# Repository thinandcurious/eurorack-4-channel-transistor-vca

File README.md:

# eurorack-4-channel-transistor-vca

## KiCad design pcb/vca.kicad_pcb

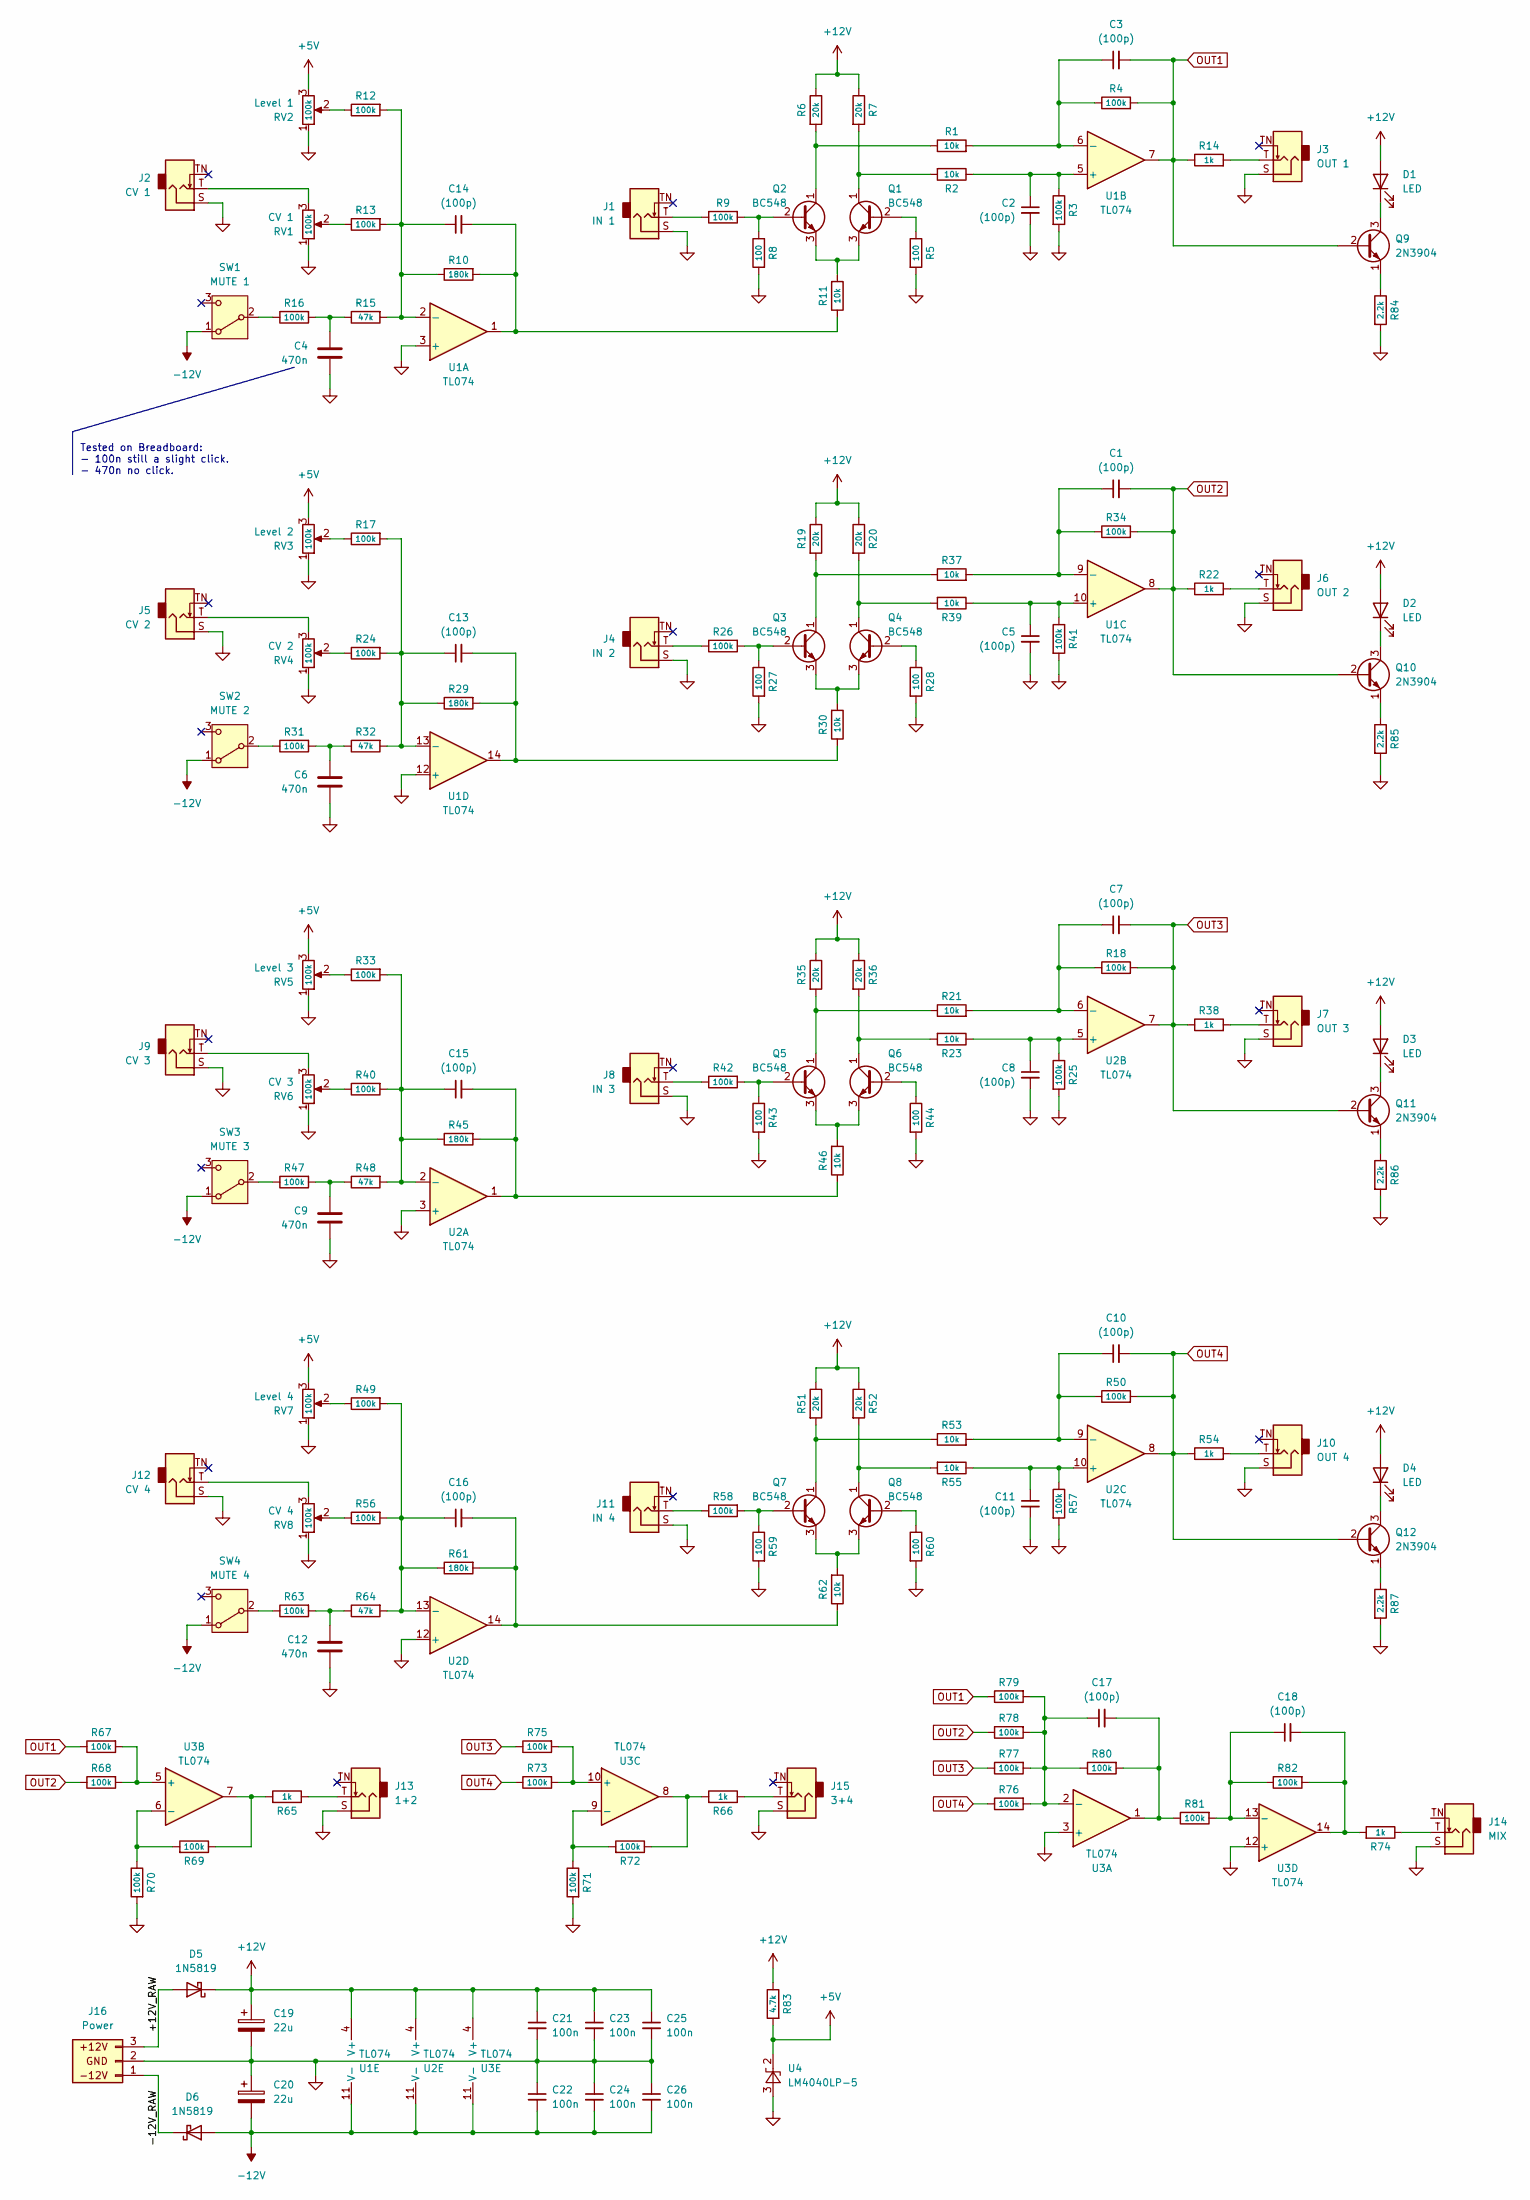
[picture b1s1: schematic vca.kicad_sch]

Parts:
C1, C2, C3, C5, C7, C8, C10, C11, C13, C14, C15, C16, C17, C18: (100p); C_0805_HandSolder
C4, C6, C9, C12: 470n; C_Rect_L7.2mm_W3.0mm_P5.00mm_FKS2_FKP2_MKS2_MKP2
C19, C20: 22u; CP_Radial_D6.3mm_P2.50mm
C21, C22, C23, C24, C25, C26: 100n; C_0805_HandSolder
D1, D2, D3, D4: LED; LED_D3.0mm_Centered
D5, D6: 1N5819; D_DO-41_SOD81_P7.62mm_Horizontal
J1: IN 1; Jack_3.5mm_PJ398SM_Vertical
J2: CV 1; Jack_3.5mm_PJ398SM_Vertical
J3: OUT 1; Jack_3.5mm_PJ398SM_Vertical
J4: IN 2; Jack_3.5mm_PJ398SM_Vertical
J5: CV 2; Jack_3.5mm_PJ398SM_Vertical
J6: OUT 2; Jack_3.5mm_PJ398SM_Vertical
J7: OUT 3; Jack_3.5mm_PJ398SM_Vertical
J8: IN 3; Jack_3.5mm_PJ398SM_Vertical
J9: CV 3; Jack_3.5mm_PJ398SM_Vertical
J10: OUT 4; Jack_3.5mm_PJ398SM_Vertical
J11: IN 4; Jack_3.5mm_PJ398SM_Vertical
J12: CV 4; Jack_3.5mm_PJ398SM_Vertical
J13: 1+2; Jack_3.5mm_PJ398SM_Vertical
J14: MIX; Jack_3.5mm_PJ398SM_Vertical
J15: 3+4; Jack_3.5mm_PJ398SM_Vertical
J16: Power; JST_XH_B3B-XH-A_1x03_P2.50mm_Vertical
Q1, Q2, Q3, Q4, Q5, Q6, Q7, Q8: BC548; TO-92_Inline_Wide
Q9, Q10, Q11, Q12: 2N3904; TO-92_Inline_Wide
R1, R2, R11, R21, R23, R30, R37, R39, R46, R53, R55, R62: 10k; R_Axial_DIN0207_L6.3mm_D2.5mm_P7.62mm_Horizontal
R3, R4, R9, R12, R13, R16, R17, R18, R24, R25, R26, R31, R33, R34, R40, R41, R42, R47, R49, R50, R56, R57, R58, R63, R67, R68, R69, R70, R71, R72, R73, R75, R76, R77, R78, R79, R80, R81, R82: 100k; R_Axial_DIN0207_L6.3mm_D2.5mm_P7.62mm_Horizontal
R5, R8, R27, R28, R43, R44, R59, R60: 100; R_Axial_DIN0207_L6.3mm_D2.5mm_P7.62mm_Horizontal
R6, R7, R19, R20, R35, R36, R51, R52: 20k; R_Axial_DIN0207_L6.3mm_D2.5mm_P7.62mm_Horizontal
R10, R29, R45, R61: 180k; R_Axial_DIN0207_L6.3mm_D2.5mm_P7.62mm_Horizontal
R14, R22, R38, R54, R65, R66, R74: 1k; R_Axial_DIN0207_L6.3mm_D2.5mm_P7.62mm_Horizontal
R15, R32, R48, R64: 47k; R_Axial_DIN0207_L6.3mm_D2.5mm_P7.62mm_Horizontal
R83: 4.7k; R_Axial_DIN0207_L6.3mm_D2.5mm_P7.62mm_Horizontal
R84, R85, R86, R87: 2.2k; R_Axial_DIN0207_L6.3mm_D2.5mm_P7.62mm_Horizontal
RV1, RV2, RV3, RV4, RV5, RV6, RV7, RV8: 100k; Potentiometer_Alpha_RD901F
SW1: MUTE 1; Switch_SPDT_Micro-Toggle
SW2: MUTE 2; Switch_SPDT_Micro-Toggle
SW3: MUTE 3; Switch_SPDT_Micro-Toggle
SW4: MUTE 4; Switch_SPDT_Micro-Toggle
U1, U2, U3: TL074; DIP-14_W7.62mm
U4: LM4040LP-5; TO-92_Inline_Wide

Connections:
+5V: R83.2, RV2.3, RV3.3, RV5.3, RV7.3, U4.2 (K)
+12V: C19.1, C21.1, C23.1, C25.1, D1.2 (A), D2.2 (A), D3.2 (A), D4.2 (A), D5.1 (K), R6.1, R7.1, R19.1, R20.1, R35.1, R36.1, R51.1, R52.1, R83.1, U1.4 (V+), U2.4 (V+), U3.4 (V+)
-12V: C20.2, C22.2, C24.2, C26.2, D6.2 (A), SW1.1 (A), SW2.1 (A), SW3.1 (A), SW4.1 (A), U1.11 (V-), U2.11 (V-), U3.11 (V-)
/+12V_RAW: D5.2 (A), J16.3
/-12V_RAW: D6.1 (K), J16.1
GND: C2.2, C4.2, C5.2, C6.2, C8.2, C9.2, C11.2, C12.2, C19.2, C20.1, C21.2, C22.1, C23.2, C24.1, C25.2, C26.1, J1.S, J2.S, J3.S, J4.S, J5.S, J6.S, J7.S, J8.S, J9.S, J10.S, J11.S, J12.S, J13.S, J14.S, J15.S, J16.2, R3.2, R5.2, R8.2, R25.2, R27.2, R28.2, R41.2, R43.2, R44.2, R57.2, R59.2, R60.2, R70.2, R71.2, R84.2, R85.2, R86.2, R87.2, RV1.1, RV2.1, RV3.1, RV4.1, RV5.1, RV6.1, RV7.1, RV8.1, U1.3 (+), U1.12 (+), U2.3 (+), U2.12 (+), U3.3 (+), U3.12 (+), U4.3 (A)
unnamed: C4.1, R15.1, R16.2
unnamed: C6.1, R31.2, R32.1
unnamed: C9.1, R47.2, R48.1
unnamed: C12.1, R63.2, R64.1
unnamed: C13.2, R29.2, R30.1, U1.14
unnamed: C14.2, R10.2, R11.1, U1.1
unnamed: C15.2, R45.2, R46.1, U2.1
unnamed: C16.2, R61.2, R62.1, U2.14
unnamed: C17.2, R80.2, R81.1, U3.1
unnamed: C18.2, R74.2, R82.2, U3.14
unnamed: D1.1 (K), Q9.3 (C)
unnamed: D2.1 (K), Q10.3 (C)
unnamed: D3.1 (K), Q11.3 (C)
unnamed: D4.1 (K), Q12.3 (C)
unnamed: J1.T, R9.1
unnamed: J2.T, RV1.3
unnamed: J3.T, R14.2
unnamed: J4.T, R26.1
unnamed: J5.T, RV4.3
unnamed: J6.T, R22.2
unnamed: J7.T, R38.2
unnamed: J8.T, R42.1
unnamed: J9.T, RV6.3
unnamed: J10.T, R54.2
unnamed: J11.T, R58.1
unnamed: J12.T, RV8.3
unnamed: J13.T, R65.1
unnamed: J14.T, R74.1
unnamed: J15.T, R66.1
unnamed: Q1.2 (B), R5.1
unnamed: Q1.1 (C), R2.2, R7.2
unnamed: Q1.3 (E), Q2.3 (E), R11.2
unnamed: Q2.2 (B), R8.1, R9.2
unnamed: Q2.1 (C), R1.1, R6.2
unnamed: Q3.2 (B), R26.2, R27.1
unnamed: Q3.1 (C), R19.2, R37.1
unnamed: Q3.3 (E), Q4.3 (E), R30.2
unnamed: Q4.2 (B), R28.1
unnamed: Q4.1 (C), R20.2, R39.2
unnamed: Q5.2 (B), R42.2, R43.1
unnamed: Q5.1 (C), R21.1, R35.2
unnamed: Q5.3 (E), Q6.3 (E), R46.2
unnamed: Q6.2 (B), R44.1
unnamed: Q6.1 (C), R23.2, R36.2
unnamed: Q7.2 (B), R58.2, R59.1
unnamed: Q7.1 (C), R51.2, R53.1
unnamed: Q7.3 (E), Q8.3 (E), R62.2
unnamed: Q8.2 (B), R60.1
unnamed: Q8.1 (C), R52.2, R55.2
unnamed: Q9.1 (E), R84.1
unnamed: Q10.1 (E), R85.1
unnamed: Q11.1 (E), R86.1
unnamed: Q12.1 (E), R87.1
unnamed: R12.1, RV2.2
unnamed: R13.1, RV1.2
unnamed: R17.1, RV3.2
unnamed: R24.1, RV4.2
unnamed: R33.1, RV5.2
unnamed: R40.1, RV6.2
unnamed: R49.1, RV7.2
unnamed: R56.1, RV8.2
unnamed: R65.2, R69.1, U3.7
unnamed: R66.2, R72.1, U3.8
unnamed: R16.1, SW1.2 (B)
unnamed: R31.1, SW2.2 (B)
unnamed: R47.1, SW3.2 (B)
unnamed: R63.1, SW4.2 (B)
unnamed: C14.1, R10.1, R12.2, R13.2, R15.2, U1.2 (-)
unnamed: C2.1, R2.1, R3.1, U1.5 (+)
unnamed: C3.1, R1.2, R4.1, U1.6 (-)
unnamed: C5.1, R39.1, R41.1, U1.10 (+)
unnamed: C1.1, R34.1, R37.2, U1.9 (-)
unnamed: C13.1, R17.2, R24.2, R29.1, R32.2, U1.13 (-)
unnamed: C15.1, R33.2, R40.2, R45.1, R48.2, U2.2 (-)
unnamed: C8.1, R23.1, R25.1, U2.5 (+)
unnamed: C7.1, R18.1, R21.2, U2.6 (-)
unnamed: C11.1, R55.1, R57.1, U2.10 (+)
unnamed: C10.1, R50.1, R53.2, U2.9 (-)
unnamed: C16.1, R49.2, R56.2, R61.1, R64.2, U2.13 (-)
unnamed: C17.1, R76.2, R77.2, R78.2, R79.2, R80.1, U3.2 (-)
unnamed: R67.2, R68.2, U3.5 (+)
unnamed: R69.2, R70.1, U3.6 (-)
unnamed: R73.2, R75.2, U3.10 (+)
unnamed: R71.1, R72.2, U3.9 (-)
unnamed: C18.1, R81.2, R82.1, U3.13 (-)
OUT1: C3.2, Q9.2 (B), R4.2, R14.1, R67.1, R79.1, U1.7
OUT2: C1.2, Q10.2 (B), R22.1, R34.2, R68.1, R78.1, U1.8
OUT3: C7.2, Q11.2 (B), R18.2, R38.1, R75.1, R77.1, U2.7
OUT4: C10.2, Q12.2 (B), R50.2, R54.1, R73.1, R76.1, U2.8

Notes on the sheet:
Tested on Breadboard: - 100n still a slight click. - 470n no click.

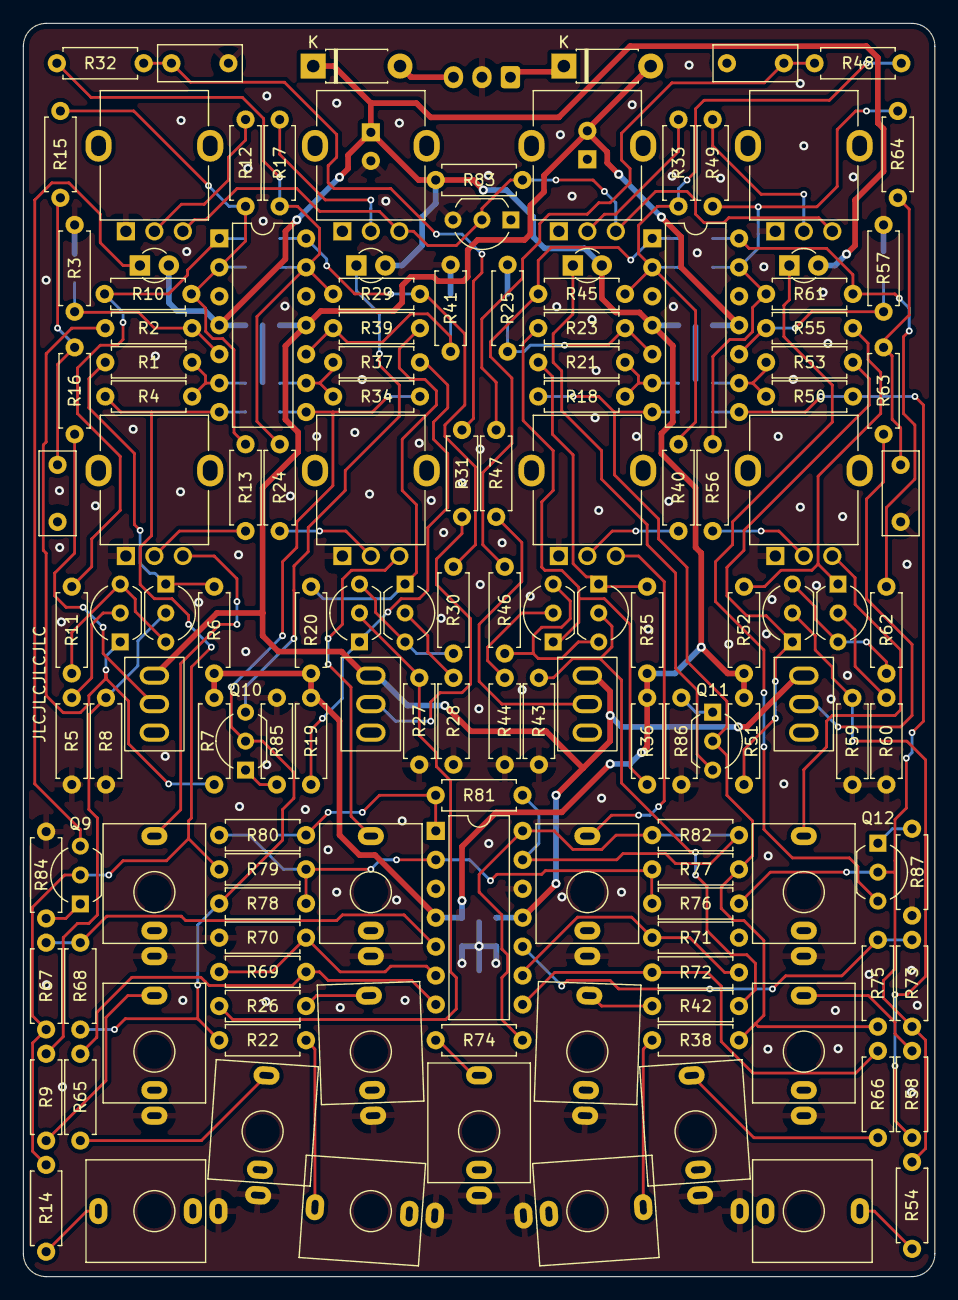
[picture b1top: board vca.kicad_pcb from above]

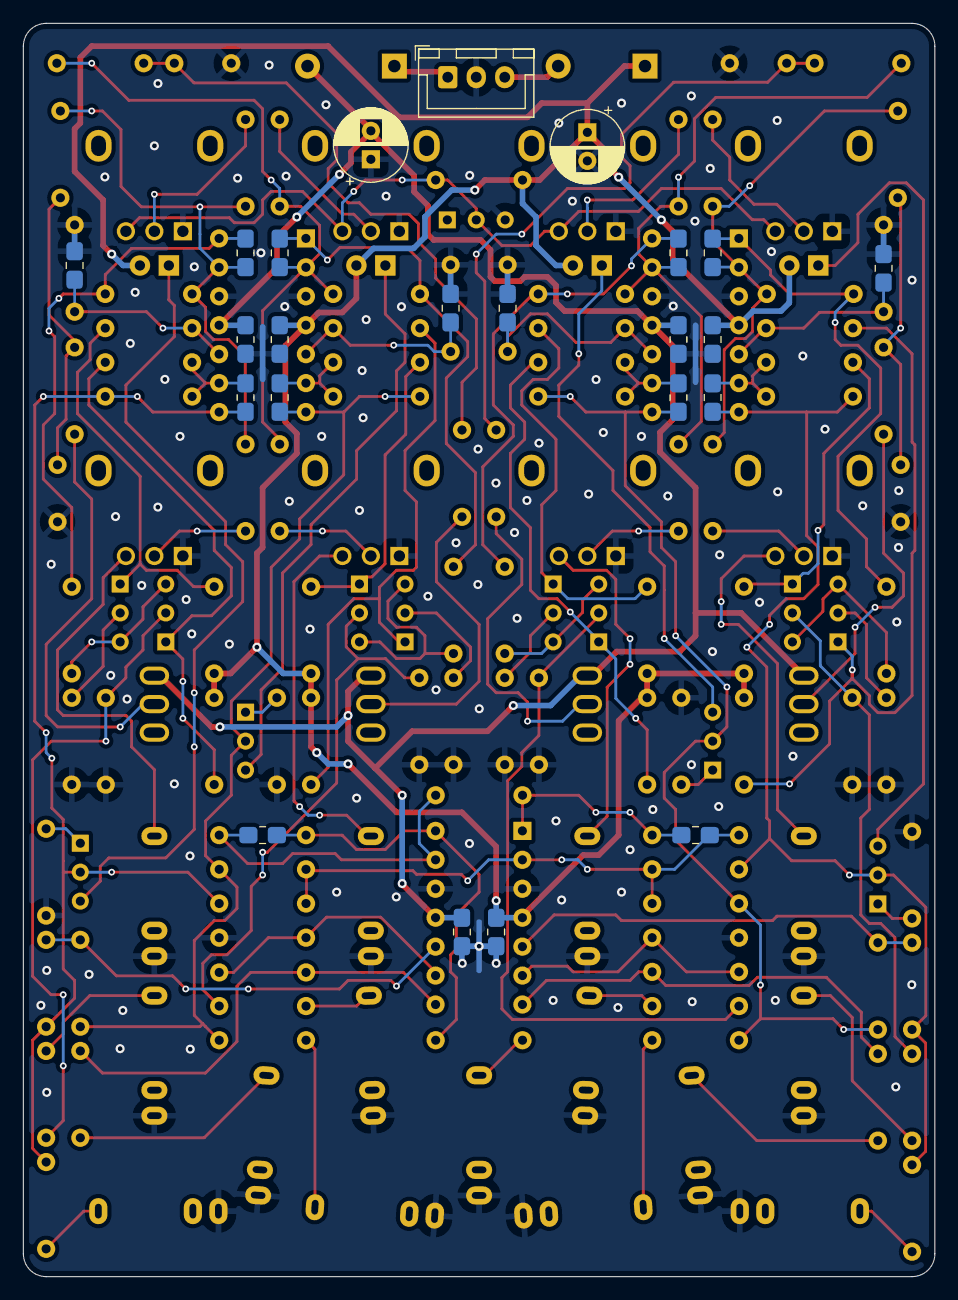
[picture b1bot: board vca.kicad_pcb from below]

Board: 2 copper layers, 80.0 x 110.0 mm, 163 parts (23 on the bottom side), 95 nets.

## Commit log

2025-03-17 upload
